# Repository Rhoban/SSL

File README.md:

# SSL - AI

## Development Guidelines

The code follows the guideline describe in ROS. [ROS_Guideline](http://wiki.ros.org/CppStyleGuide)

### Format

We using a .clang-format file. Caution ! Use the clang-format version 6.0, if your OS doesn't install it automatically then install clang-format-6.0 and rename the command to use the format script.

## Requirements

### System dependencies

You will need theses packets:

``` bash
sudo apt-get install -y g++ cmake libprotobuf-dev \
  protobuf-compiler php php-cli php-xml \
  libgtest-dev libwebsockets-dev gnuplot
```

To install the new viewer, we have conflits between the npm and the libwebsockets.
Go to here https://github.com/nodesource/distributions/blob/master/README.md and install npm.

### Catkin

Now install catkin:

``` bash
sudo apt-get install -y python-pip python-empy
# Eventually, if necessary, install python3-trollius
sudo apt-get install -y python3-trollius
sudo pip install -U catkin_tools
```

## Dependencies

After cloning this repository, run:

``` bash
./workspace setup
./workspace install
```

This will install all the dependencies.

See also clang-format above.

## Building

To build, run:

``` bash
./workspace build
```

Then, you can use the following debugging binaries:

* `./bin/vision`, to display informations from the vision (see `client/vision.cpp`)
* `./bin/referee`, to display informations from the referee (see `client/referee.cpp`)
* `./bin/sim`, to send commands to the simulator (see `client/sim.cpp`)

## Documentation

From workspace root:

``` bash
cd doc
mkdir build
cd build
cmake ..
make doc
```

Documentation is inside html directory.

## Testing

Tests can be built using the command: `./workspace tests`

To run the tests (once built), use the command: `./workspace test`

Access to the test message is controlled by adding the flag `--verbose`.

Example: Building and showing tests, but only for ssl_ai
`./workspace tests --verbose --no-deps ssl_ai`

## Packages

Here are the packages:

* `client`: the package to communicate with the SSL official software (vision, referee and simulator)
  * Note that this provides test binaries in `bin/` directory
* `viewer`: the viewer to interact with the strategies
* TODO!

## QtCreator

To use QtCreator, you have to add following line at the end of the file .workspace/SetupCommand.php:

below the line:

``` php
OS::run('catkin config --profile release -x _release --cmake-args -DCMAKE_BUILD_TYPE=Release -DCMAKE_CXX_FLAGS="-Wall -msse2"');
```

add the two lines:

``` php
OS::run('catkin config --profile qtcreator_debug -x _qtdebug --cmake-args -G"CodeBlocks - Unix Makefiles" -DCMAKE_BUILD_TYPE=Debug -DCMAKE_CXX_FLAGS="-Wall -msse2"');

OS::run('catkin config --profile qtcreator_release -x _qtrelease --cmake-args -G"CodeBlocks - Unix Makefiles" -DCMAKE_BUILD_TYPE=Release -DCMAKE_CXX_FLAGS="-Wall -msse2"');
```

This will create a debug and release profile with CodeBlocks support (needed by QtCreator).

Then:

``` bash
./workspace setup
./workspace build --profile=qtcreator_debug
./workspace build --profile=qtcreator_release
```

Now, you can load a CMakeLists.txt into QtCreator:

``` bash
qtcreator src/ai/CMakeLists.txt
```

In the configure project window, uncheck desktop and choose "import compil from..." and select `build_qtdebug/ssl_ai` then click on Import button. This will create a temporary imported kit with only one checked. You can add various setup (debug/release/...) by selecting the right building directory (i.e. build_qtrelease/ssl_ai).

Finally, click on "Configure Project" button.

If you want to reset your Qt configuration, just remove the file CMakeLists.txt.user. Also, please never add this file to the git repository.

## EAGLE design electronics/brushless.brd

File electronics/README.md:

# SSL Board

## XXX: To check!!!

- 5V tolerance for SPI
- 0-5V for maxon from 3.3??
  Add OD pullups?!
- Pull down on motors enable (or pull up?) to disable normally
- Maxon enable pin?

## Mechanics

Fixation holes are on a 126x82 rectangle, 3mm standoff

## Components

### MOS to kick

IRFPE30 (deprecated)
- http://fr.farnell.com/infineon/irfp4242pbf/transistor-mosfet-n-300v-to-247/dp/1298480

**OR** FDH44N50 (farnell 500V / 40A)
- http://fr.farnell.com/on-semiconductor-fairchild/fdh44n50/transistor-mosfet-n-to-247/dp/1095012

### NPN SOT-23 BC817 Transistors
- http://fr.farnell.com/nxp/bc817-215/transistor-npn-boitier-sot-23/dp/1081223

### TRACOPOWER TSR 1-2450 5V/1A Switching
- http://fr.farnell.com/tracopower/tsr-1-2450/convertisseur-dc-dc5v1asip/dp/1696320

### TRACOPOWER TSR 1-2433 3.3V/1A Switching

- http://fr.farnell.com/tracopower/tsr-1-2433/converter-dc-to-dc-3-3v-1a-sip/dp/1696319

### ~6.6mm pitch buzzer

- AliExpress ("passive buzzer") are typically 6.6mm pitch

### Infrared barrier (5mm LEDs/photodiode)

- Emit (100mA): http://fr.farnell.com/vishay/tsal6200/emetteur-ir-940nm-5mm-traversant/dp/3152856
- Receive: http://fr.farnell.com/osram/sfh213-fa/photodiode-ir-filtree/dp/1212763

### Quartz 40Mhz pour LS7366R-S

- http://fr.farnell.com/abracon/abl-40-000mhz-b2/crystal-40m-18pf-cl-hc49-4h/dp/1611785

### Multiplexers CD4051BM

- http://fr.farnell.com/texas-instruments/cd4051bm/circuit-logique-cmos-4000/dp/8388970

## Passives

- 0603 15pF capacitors
    - http://fr.farnell.com/multicomp/mcwr08x3300ftl/res-couche-epaisse-330r-1-0-125w/dp/2446955
- 0805 100 ohms resistor (stacked x3)
    -  http://fr.farnell.com/vishay/crcw080562r0fkea/res-couche-epaisse-62r-1-0-125w/dp/2138819
- 47uF decoupling capacitor
    - http://fr.farnell.com/panasonic-electronic-components/eee1ca470sp/condensateur-elec-alu-47uf-16v/dp/9696946

- 0805 1K resistor
- 0805 2K resistor
- 0805 3K resistor
- 0805 10K resistor

## Connectors

### 0.1" Header 2x8, right angle (communication modules)

- http://fr.farnell.com/samtec/ssw-104-02-g-d-ra/embase-2-54mm-coudee-double-8voies/dp/1668343

Or, for "on the table" version    

- http://fr.farnell.com/multicomp/2214s-08sg-85/fiche-femelle-ci-2-rangee-vert/dp/1593489

### 0.1" Header 1x8 + 0.1" Header 2x9 (maxon)

- http://fr.farnell.com/multicomp/2212s-08sg-85/fiche-femelle-ci-1-rangee-8voies/dp/1593463
- http://fr.farnell.com/samtec/bcs-109-l-d-te/femelle-2-54mm-vertical-18-voies/dp/2308429

### 0.1" Header 1x8 (IMU)

- http://fr.farnell.com/multicomp/2212s-08sg-85/fiche-femelle-ci-1-rangee-8voies/dp/1593463

### 0.1" Header 1x20 (Maple mini)

- http://fr.farnell.com/multicomp/2212s-20sg-85/fiche-femelle-ci-1-rangee-20voies/dp/1593469

### JST-XH 10 pins (2.54mm pitch)

- http://www.ebay.fr/itm/20-sets-JST-ZH-PH-XH-1-0-1-25MM-1-5-2-0-2-5-2p-6P-FemaleConnector-Plug-w-Wire/272410498870

### JST-ZH 2pin (1.5mm pitch)

- http://www.ebay.fr/itm/20-sets-JST-ZH-PH-XH-1-0-1-25MM-1-5-2-0-2-5-2p-6P-FemaleConnector-Plug-w-Wire/272410498870

### XT-60

- http://www.ebay.fr/itm/5-PAIRES-XT60-Connecteur-Prise-RC-Batterie-Accu-LiPO-Plug-3-5mm-Bullet-Connector/222301985053

## Sub-boards

- Maple mini
- GY-85
- Maxon 380200
- NRF24L01 modules
- Voltage booster (can be easily found with keywords "390V booster")

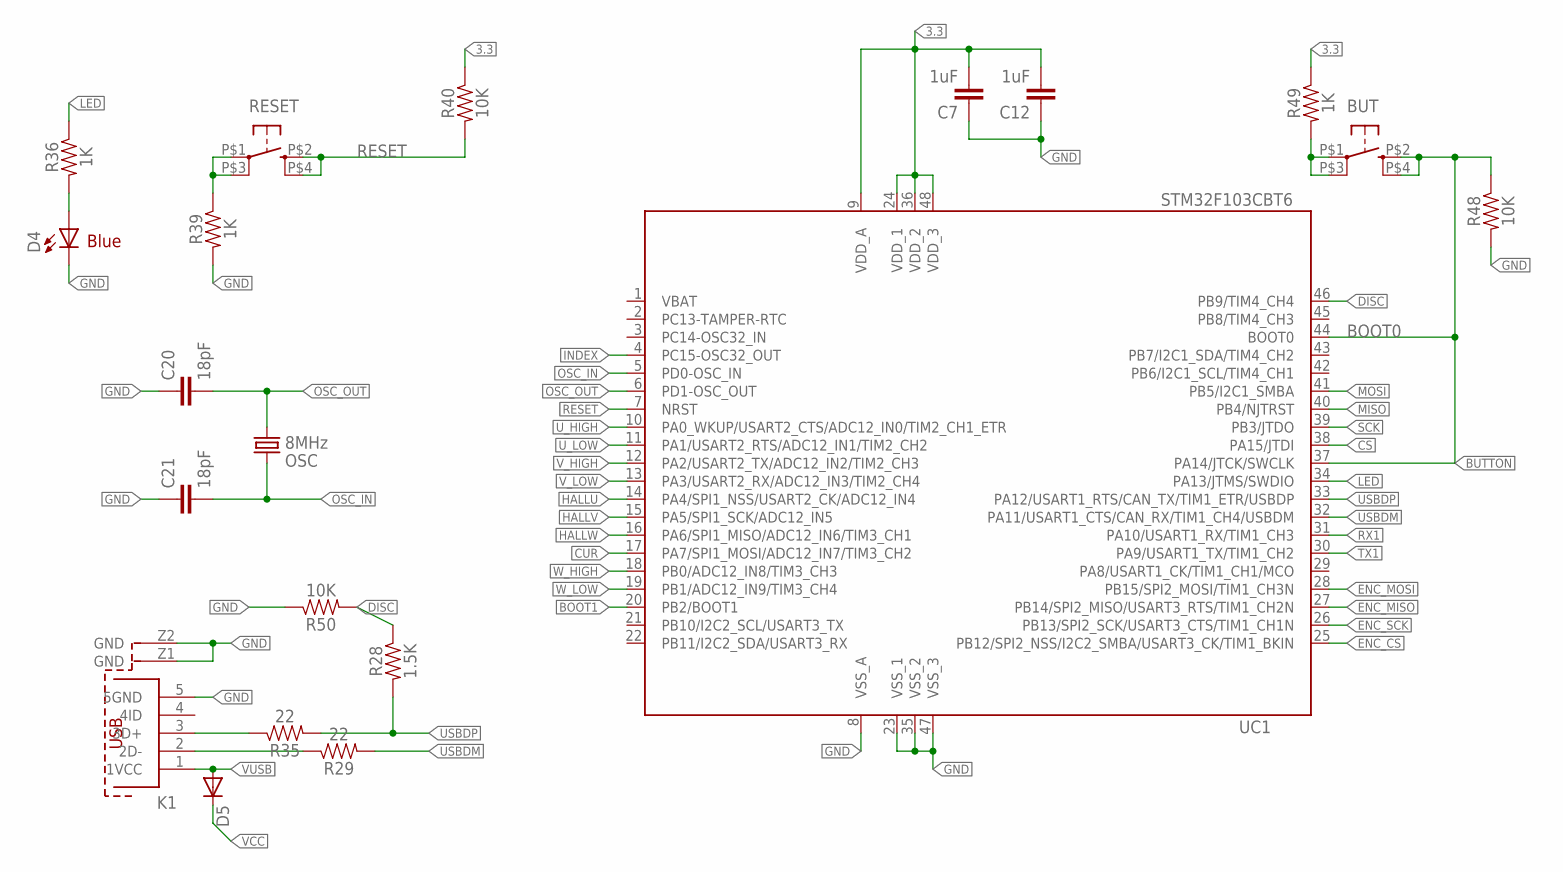
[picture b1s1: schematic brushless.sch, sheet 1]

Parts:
BUT: KMR211GLFS; PUSHBUTTON-KMR241GLFS; FARNELL 1437637
C7, C12: 1uF; 0805@1; FARNELL 2496946
C20, C21: 18pF; 0805@1; FARNELL 1414620
D4: Blue; LED-1206; FARNELL 1581233
D5: DIODESOD; SOD-323; FARNELL 8737843RL
K1: 614105150721; FARNELL 2470830
OSC: 8MHz; CRYSTAL-SMD-5X3; FARNELL 2467818
R28: 1.5K; 0805; FARNELL 2446909
R29, R35: 22; 0805; FARNELL 2446926
R36, R39, R49: 1K; 0805; FARNELL 2446904
R40, R48, R50: 10K; 0805; FARNELL 2447553
RESET: KMR211GLFS; PUSHBUTTON-KMR241GLFS; FARNELL 1437637
UC1: STM32F103CBT6; LQFP48; FARNELL 1606327

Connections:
3.3: C7.2, C12.2, R40.1, R49.1, UC1.9 (VDD_A), UC1.24 (VDD_1), UC1.36 (VDD_2), UC1.48 (VDD_3); also elsewhere on the board
BOOT1: UC1.20 (PB2/BOOT1)
BUTTON: BUT.P$2 (2), BUT.P$4 (4), R48.1, UC1.37 (PA14/JTCK/SWCLK), UC1.44 (BOOT0)
CS: UC1.38 (PA15/JTDI); also elsewhere on the board
CUR: UC1.17 (PA7/SPI1_MOSI/ADC12_IN7/TIM3_CH2); also elsewhere on the board
DISC: R28.1, R50.2, UC1.46 (PB9/TIM4_CH4)
ENC_CS: UC1.25 (PB12/SPI2_NSS/I2C2_SMBA/USART3_CK/TIM1_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); also elsewhere on the board
ENC_MISO: UC1.27 (PB14/SPI2_MISO/USART3_RTS/TIM1_CH2N); also elsewhere on the board
ENC_MOSI: UC1.28 (PB15/SPI2_MOSI/TIM1_CH3N); also elsewhere on the board
ENC_SCK: UC1.26 (PB13/SPI2_SCK/USART3_CTS/TIM1_CH1N); also elsewhere on the board
GND: C7.1, C12.1, C20.1, C21.1, D4.C, K1.5 (5GND), K1.Z1 (GND), K1.Z2 (GND), R39.2, R48.2, R50.1, UC1.8 (VSS_A), UC1.23 (VSS_1), UC1.35 (VSS_2), UC1.47 (VSS_3); also elsewhere on the board
HALLU: UC1.14 (PA4/SPI1_NSS/USART2_CK/ADC12_IN4); also elsewhere on the board
HALLV: UC1.15 (PA5/SPI1_SCK/ADC12_IN5); also elsewhere on the board
HALLW: UC1.16 (PA6/SPI1_MISO/ADC12_IN6/TIM3_CH1); also elsewhere on the board
INDEX: UC1.4 (PC15-OSC32_OUT); also elsewhere on the board
LED: R36.1, UC1.34 (PA13/JTMS/SWDIO)
MISO: UC1.40 (PB4/NJTRST); also elsewhere on the board
MOSI: UC1.41 (PB5/I2C1_SMBA); also elsewhere on the board
unnamed: R39.1, RESET.P$1 (1), RESET.P$3 (3)
unnamed: BUT.P$1 (1), BUT.P$3 (3), R49.2
unnamed: D4.A, R36.2
unnamed: K1.2 (2D-), R29.1
unnamed: K1.3 (3D+), R35.1
OSC_IN: C21.2, OSC.3 (2), UC1.5 (PD0-OSC_IN)
OSC_OUT: C20.2, OSC.1, UC1.6 (PD1-OSC_OUT)
RESET: R40.2, RESET.P$2 (2), RESET.P$4 (4), UC1.7 (NRST)
RX1: UC1.31 (PA10/USART1_RX/TIM1_CH3)
SCK: UC1.39 (PB3/JTDO); also elsewhere on the board
TX1: UC1.30 (PA9/USART1_TX/TIM1_CH2)
USBDM: R29.2, UC1.32 (PA11/USART1_CTS/CAN_RX/TIM1_CH4/USBDM)
USBDP: R28.2, R35.2, UC1.33 (PA12/USART1_RTS/CAN_TX/TIM1_ETR/USBDP)
U_HIGH: UC1.10 (PA0_WKUP/USART2_CTS/ADC12_IN0/TIM2_CH1_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); also elsewhere on the board
U_LOW: UC1.11 (PA1/USART2_RTS/ADC12_IN1/TIM2_CH2); also elsewhere on the board
VBAT: UC1.1 (VBAT)
VCC: D5.1 (C); also elsewhere on the board
VUSB: D5.2 (A), K1.1 (1VCC)
V_HIGH: UC1.12 (PA2/USART2_TX/ADC12_IN2/TIM2_CH3); also elsewhere on the board
V_LOW: UC1.13 (PA3/USART2_RX/ADC12_IN3/TIM2_CH4); also elsewhere on the board
W_HIGH: UC1.18 (PB0/ADC12_IN8/TIM3_CH3); also elsewhere on the board
W_LOW: UC1.19 (PB1/ADC12_IN9/TIM3_CH4); also elsewhere on the board

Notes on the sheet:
BOOT0
Blue

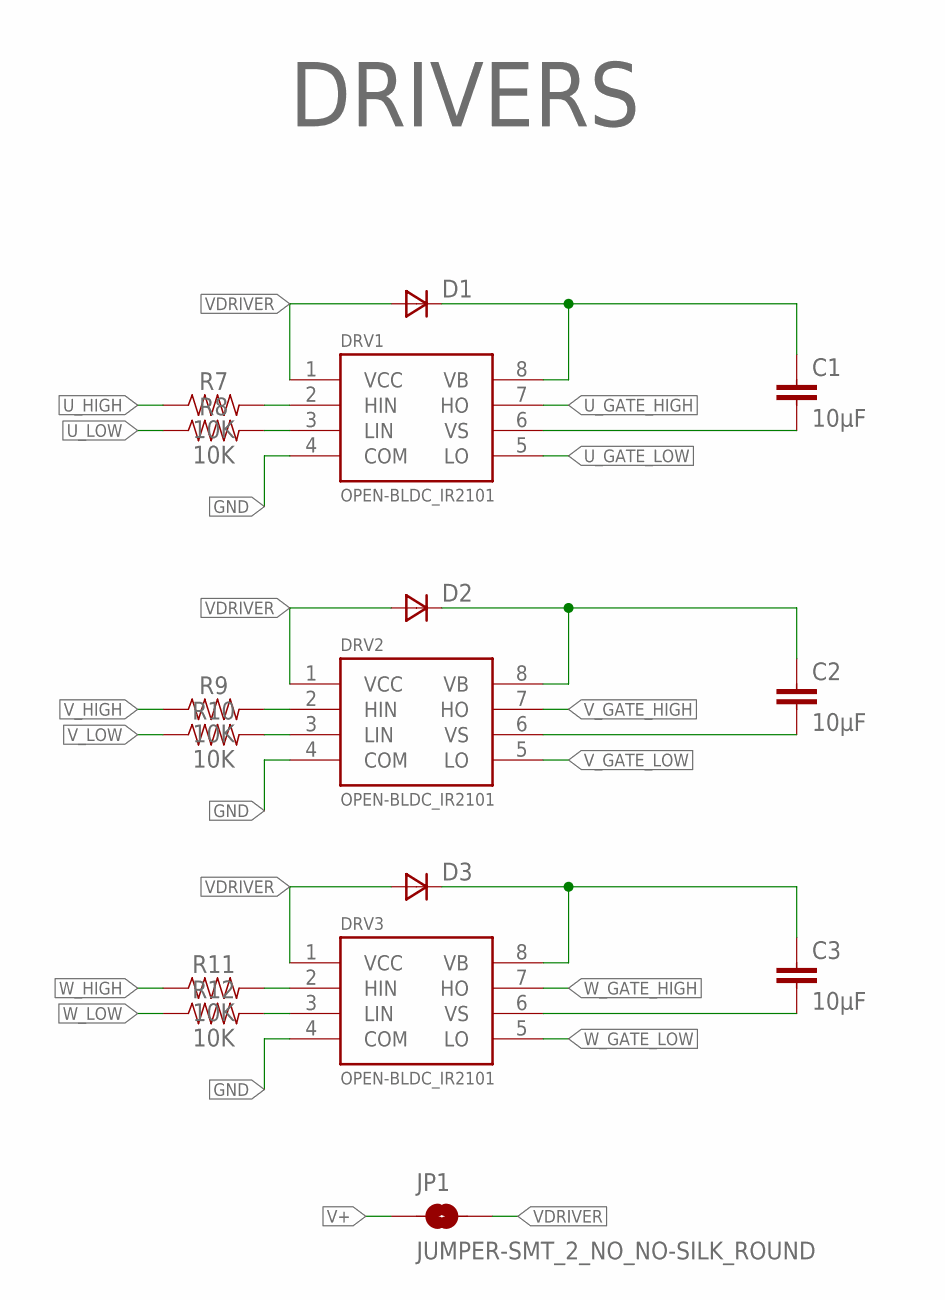
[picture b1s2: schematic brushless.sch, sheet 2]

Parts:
C1, C2, C3: 10µF; 0805; FARNELL 2528772
D1, D2, D3: ZETEX_VAR2SOT23; ZETEX_SOT-23; FARNELL 2317446
DRV1, DRV2, DRV3: OPEN-BLDC_IR2101; OPEN-BLDC_SO-8; FARNELL 2296000
JP1: JUMPER-SMT_2_NO_NO-SILK_ROUND; SMT-JUMPER_2_NO_NO-SILK_ROUND
R7, R8, R9, R10, R11, R12: 10K; 0805; FARNELL 2447553

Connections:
GND: DRV1.4 (COM), DRV2.4 (COM), DRV3.4 (COM); also elsewhere on the board
unnamed: DRV1.2 (HIN), R7.2
unnamed: C1.1, D1.1 (C), DRV1.8 (VB)
unnamed: DRV1.3 (LIN), R8.2
unnamed: C2.1, D2.1 (C), DRV2.8 (VB)
unnamed: C1.2, DRV1.6 (VS)
unnamed: DRV2.2 (HIN), R9.2
unnamed: DRV2.3 (LIN), R10.2
unnamed: C2.2, DRV2.6 (VS)
unnamed: C3.1, D3.1 (C), DRV3.8 (VB)
unnamed: DRV3.2 (HIN), R11.2
unnamed: DRV3.3 (LIN), R12.2
unnamed: C3.2, DRV3.6 (VS)
U_GATE_HIGH: DRV1.7 (HO); also elsewhere on the board
U_GATE_LOW: DRV1.5 (LO); also elsewhere on the board
U_HIGH: R7.1; also elsewhere on the board
U_LOW: R8.1; also elsewhere on the board
V+: JP1.1; also elsewhere on the board
VDRIVER: D1.3 (A), D2.3 (A), D3.3 (A), DRV1.1 (VCC), DRV2.1 (VCC), DRV3.1 (VCC), JP1.2; also elsewhere on the board
V_GATE_HIGH: DRV2.7 (HO); also elsewhere on the board
V_GATE_LOW: DRV2.5 (LO); also elsewhere on the board
V_HIGH: R9.1; also elsewhere on the board
V_LOW: R10.1; also elsewhere on the board
W_GATE_HIGH: DRV3.7 (HO); also elsewhere on the board
W_GATE_LOW: DRV3.5 (LO); also elsewhere on the board
W_HIGH: R11.1; also elsewhere on the board
W_LOW: R12.1; also elsewhere on the board

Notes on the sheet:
DRIVERS

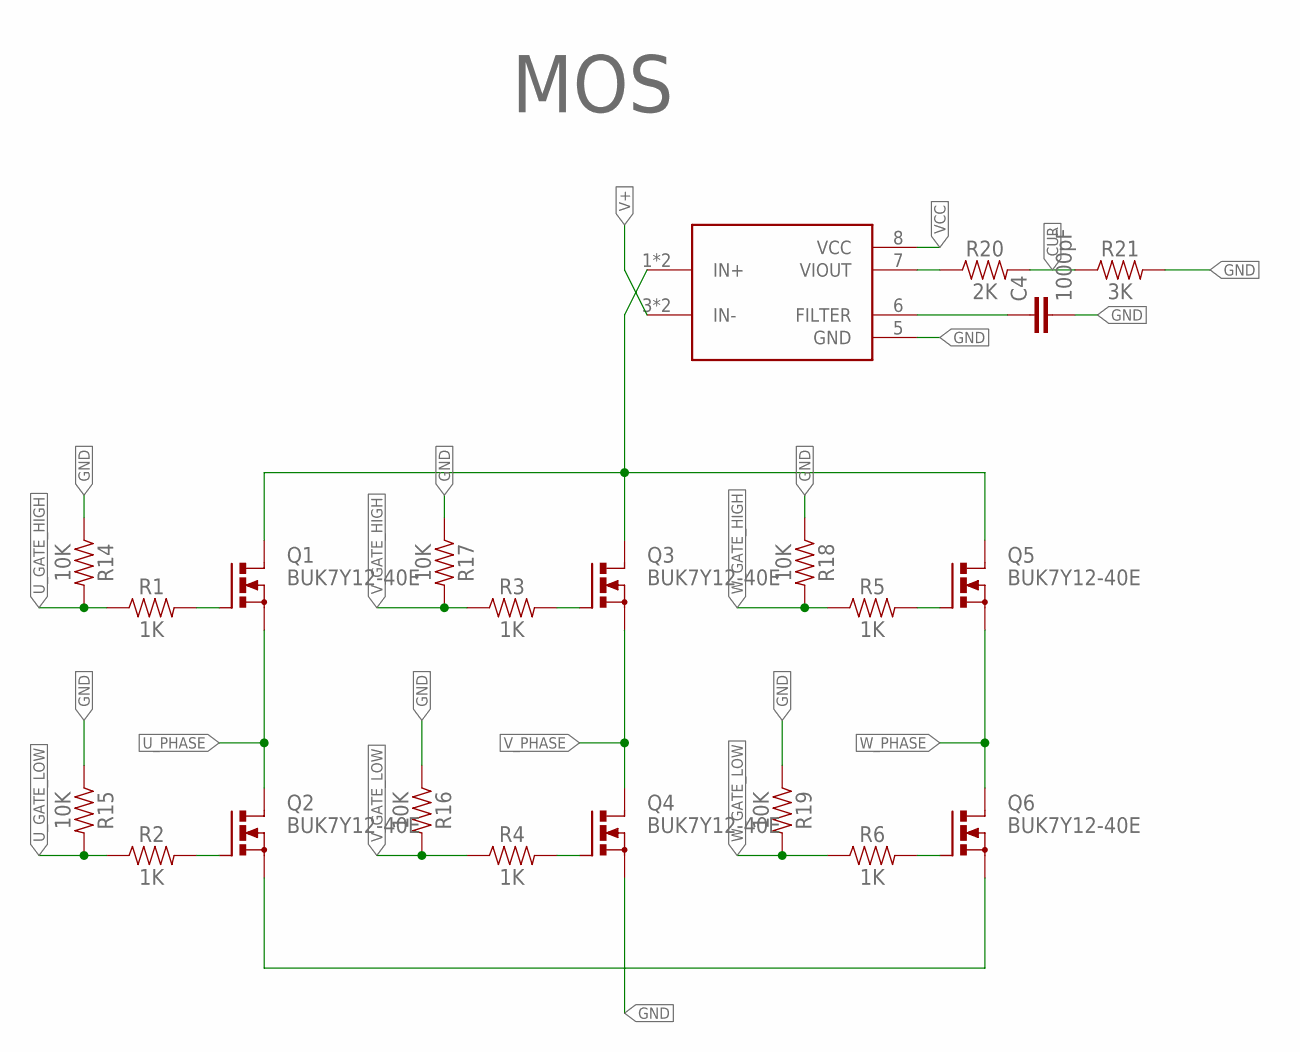
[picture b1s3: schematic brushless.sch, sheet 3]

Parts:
C4: 1000pF; 0805@1; FARNELL 2496935
Q1, Q2, Q3, Q4, Q5, Q6: BUK7Y12-40E; SOT669; FARNELL 2319916
R1, R2, R3, R4, R5, R6: 1K; 0805; FARNELL 2446904
R14, R15, R16, R17, R18, R19: 10K; 0805; FARNELL 2447553
R20: 2K; 0805; FARNELL 2446939
R21: 3K; 0805; FARNELL 2446965
SENSE: ACS712; SO8; FARNELL 1329624

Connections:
CUR: R20.2, R21.1; also elsewhere on the board
GND: C4.2, Q2.1 (S), Q2.2 (S), Q2.3 (S), Q4.1 (S), Q4.2 (S), Q4.3 (S), Q6.1 (S), Q6.2 (S), Q6.3 (S), R14.1, R15.1, R16.1, R17.1, R18.1, R19.1, R21.2, SENSE.5 (GND); also elsewhere on the board
unnamed: Q1.4 (G), R1.2
unnamed: Q3.4 (G), R3.2
unnamed: Q2.4 (G), R2.2
unnamed: Q4.4 (G), R4.2
unnamed: Q5.4 (G), R5.2
unnamed: Q6.4 (G), R6.2
unnamed: R20.1, SENSE.7 (VIOUT)
unnamed: C4.1, SENSE.6 (FILTER)
U_GATE_HIGH: R1.1, R14.2; also elsewhere on the board
U_GATE_LOW: R2.1, R15.2; also elsewhere on the board
U_PHASE: Q1.1 (S), Q1.2 (S), Q1.3 (S), Q2.MB (D); also elsewhere on the board
V+: SENSE.3 (IN-), SENSE.4 (IN-); also elsewhere on the board
V+_MOS: Q1.MB (D), Q3.MB (D), Q5.MB (D), SENSE.1 (IN+), SENSE.2 (IN+)
VCC: SENSE.8 (VCC); also elsewhere on the board
V_GATE_HIGH: R3.1, R17.2; also elsewhere on the board
V_GATE_LOW: R4.1, R16.2; also elsewhere on the board
V_PHASE: Q3.1 (S), Q3.2 (S), Q3.3 (S), Q4.MB (D); also elsewhere on the board
W_GATE_HIGH: R5.1, R18.2; also elsewhere on the board
W_GATE_LOW: R6.1, R19.2; also elsewhere on the board
W_PHASE: Q5.1 (S), Q5.2 (S), Q5.3 (S), Q6.MB (D); also elsewhere on the board

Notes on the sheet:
MOS

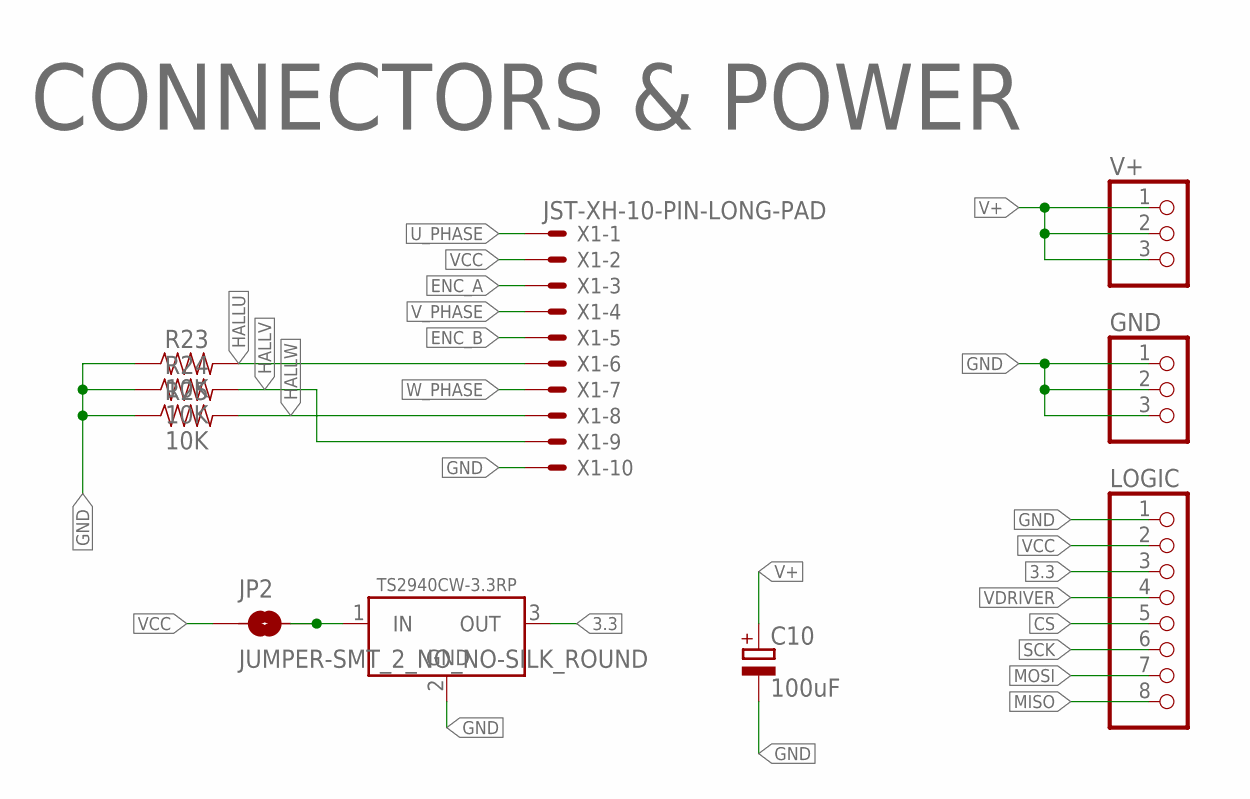
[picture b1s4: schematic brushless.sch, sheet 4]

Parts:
C10: 100uF; E3,5-8; FARNELL 1144713
GND: CONNEC_1X03; FARNELL 1022248
JP2: JUMPER-SMT_2_NO_NO-SILK_ROUND; SMT-JUMPER_2_NO_NO-SILK_ROUND
LOGIC: CONNEC_1X08; FARNELL 1022256
R23, R24, R25: 10K; 0805; FARNELL 2447553
REG1: TS2940CW-3.3RP; SOT223; FARNELL 7261403
V+: CONNEC_1X03; FARNELL 1022248
X1: JST-XH-10-PIN-LONG-PAD; JST-XH-10-PACKAGE-LONG-PAD

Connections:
3.3: LOGIC.3, REG1.3 (OUT); also elsewhere on the board
CS: LOGIC.5; also elsewhere on the board
ENC_A: X1.3; also elsewhere on the board
ENC_B: X1.5; also elsewhere on the board
GND: C10.-, GND.1, GND.2, GND.3, LOGIC.1, R23.1, R24.1, R25.1, REG1.2 (GND), X1.10; also elsewhere on the board
HALLU: R23.2, X1.6; also elsewhere on the board
HALLV: R24.2, X1.9; also elsewhere on the board
HALLW: R25.2, X1.8; also elsewhere on the board
MISO: LOGIC.8; also elsewhere on the board
MOSI: LOGIC.7; also elsewhere on the board
unnamed: JP2.2, REG1.1 (IN)
SCK: LOGIC.6; also elsewhere on the board
U_PHASE: X1.1; also elsewhere on the board
V+: C10.+, V+.1, V+.2, V+.3; also elsewhere on the board
VCC: JP2.1, LOGIC.2, X1.2; also elsewhere on the board
VDRIVER: LOGIC.4; also elsewhere on the board
V_PHASE: X1.4; also elsewhere on the board
W_PHASE: X1.7; also elsewhere on the board

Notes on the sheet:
CONNECTORS & POWER

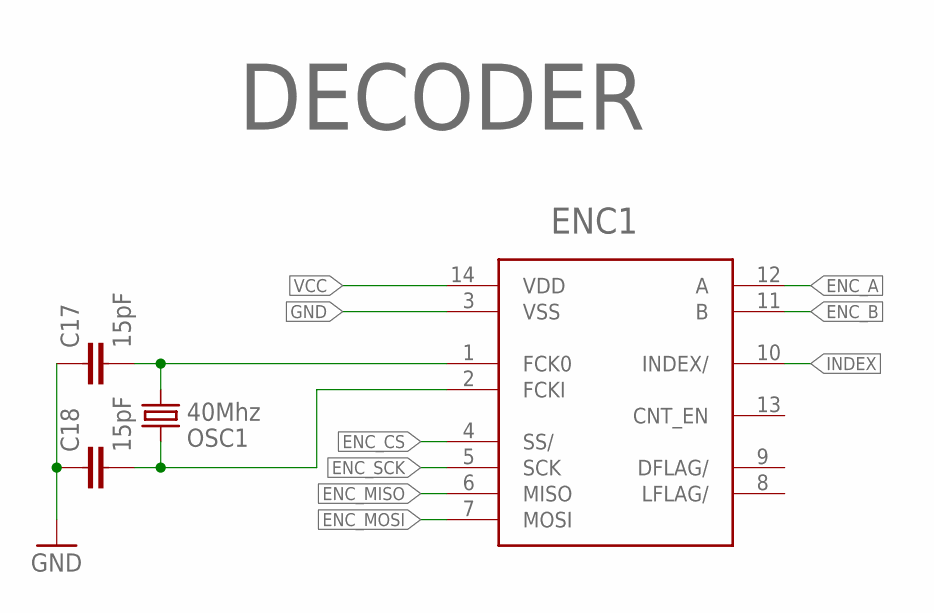
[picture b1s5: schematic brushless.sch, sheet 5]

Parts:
C17, C18: 15pF; C0603; FARNELL 721980
ENC1: LS7366RSO14; SO14
OSC1: 40Mhz; CRYSTAL-SMD-5X3; FARNELL 1842013

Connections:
ENC_A: ENC1.12 (A); also elsewhere on the board
ENC_B: ENC1.11 (B); also elsewhere on the board
ENC_CS: ENC1.4 (SS/); also elsewhere on the board
ENC_MISO: ENC1.6 (MISO); also elsewhere on the board
ENC_MOSI: ENC1.7 (MOSI); also elsewhere on the board
ENC_SCK: ENC1.5 (SCK); also elsewhere on the board
GND: C17.1, C18.1, ENC1.3 (VSS); also elsewhere on the board
INDEX: ENC1.10 (INDEX/); also elsewhere on the board
unnamed: C17.2, ENC1.1 (FCK0), OSC1.1
unnamed: C18.2, ENC1.2 (FCKI), OSC1.3 (2)
VCC: ENC1.14 (VDD); also elsewhere on the board

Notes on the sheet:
DECODER

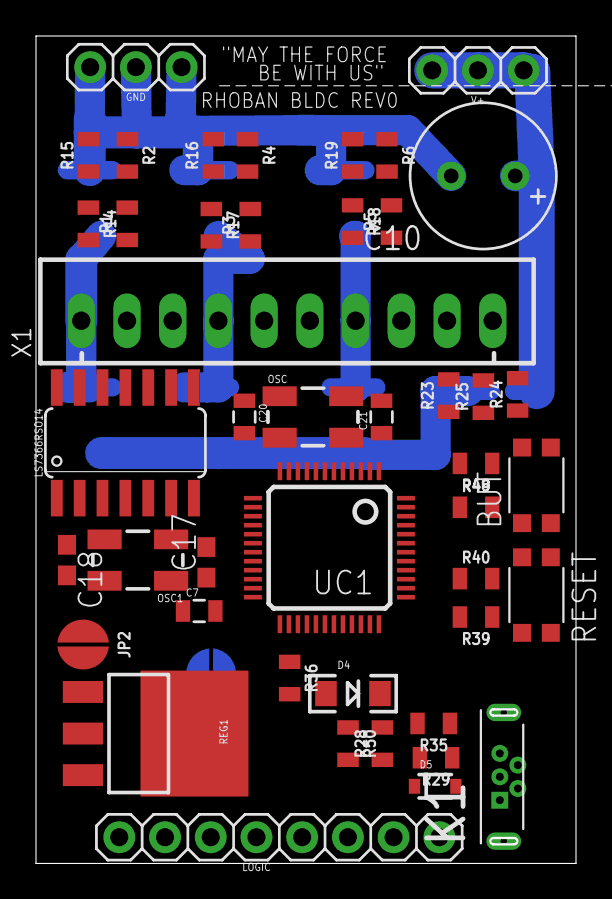
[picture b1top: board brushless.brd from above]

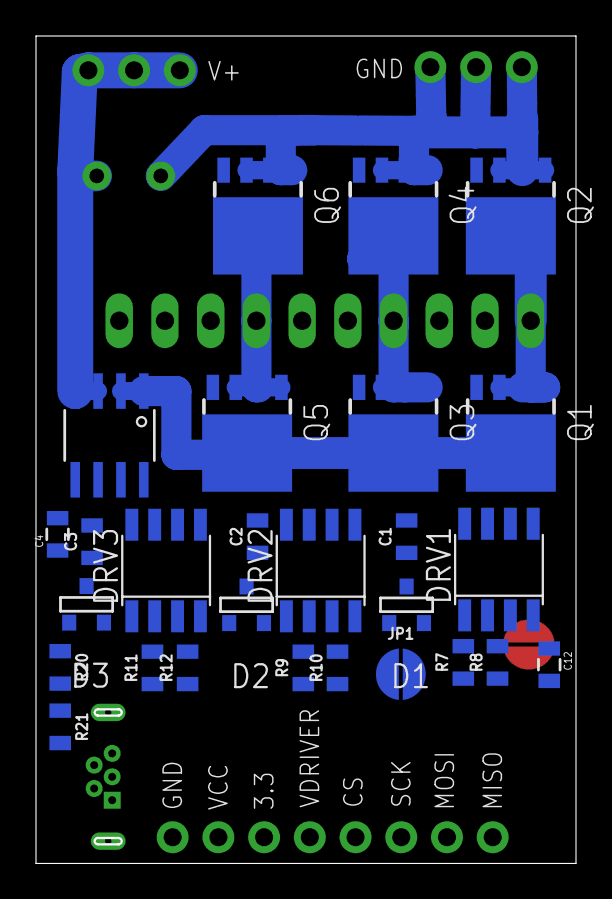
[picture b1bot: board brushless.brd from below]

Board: 4 copper layers, 30.0 x 46.0 mm, 72 parts (27 on the bottom side), 73 nets.

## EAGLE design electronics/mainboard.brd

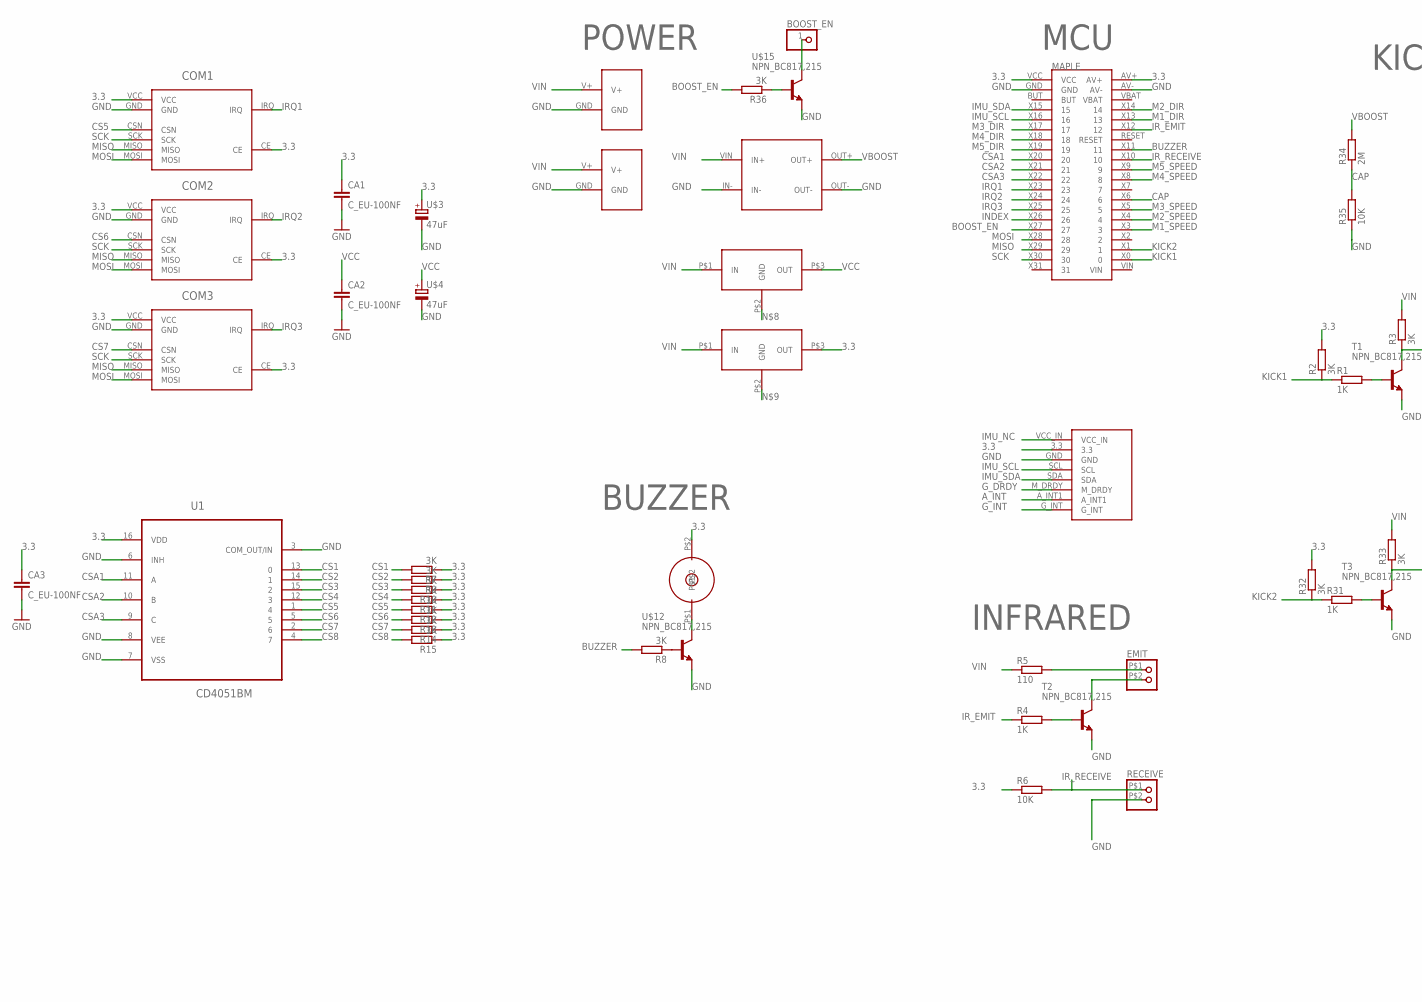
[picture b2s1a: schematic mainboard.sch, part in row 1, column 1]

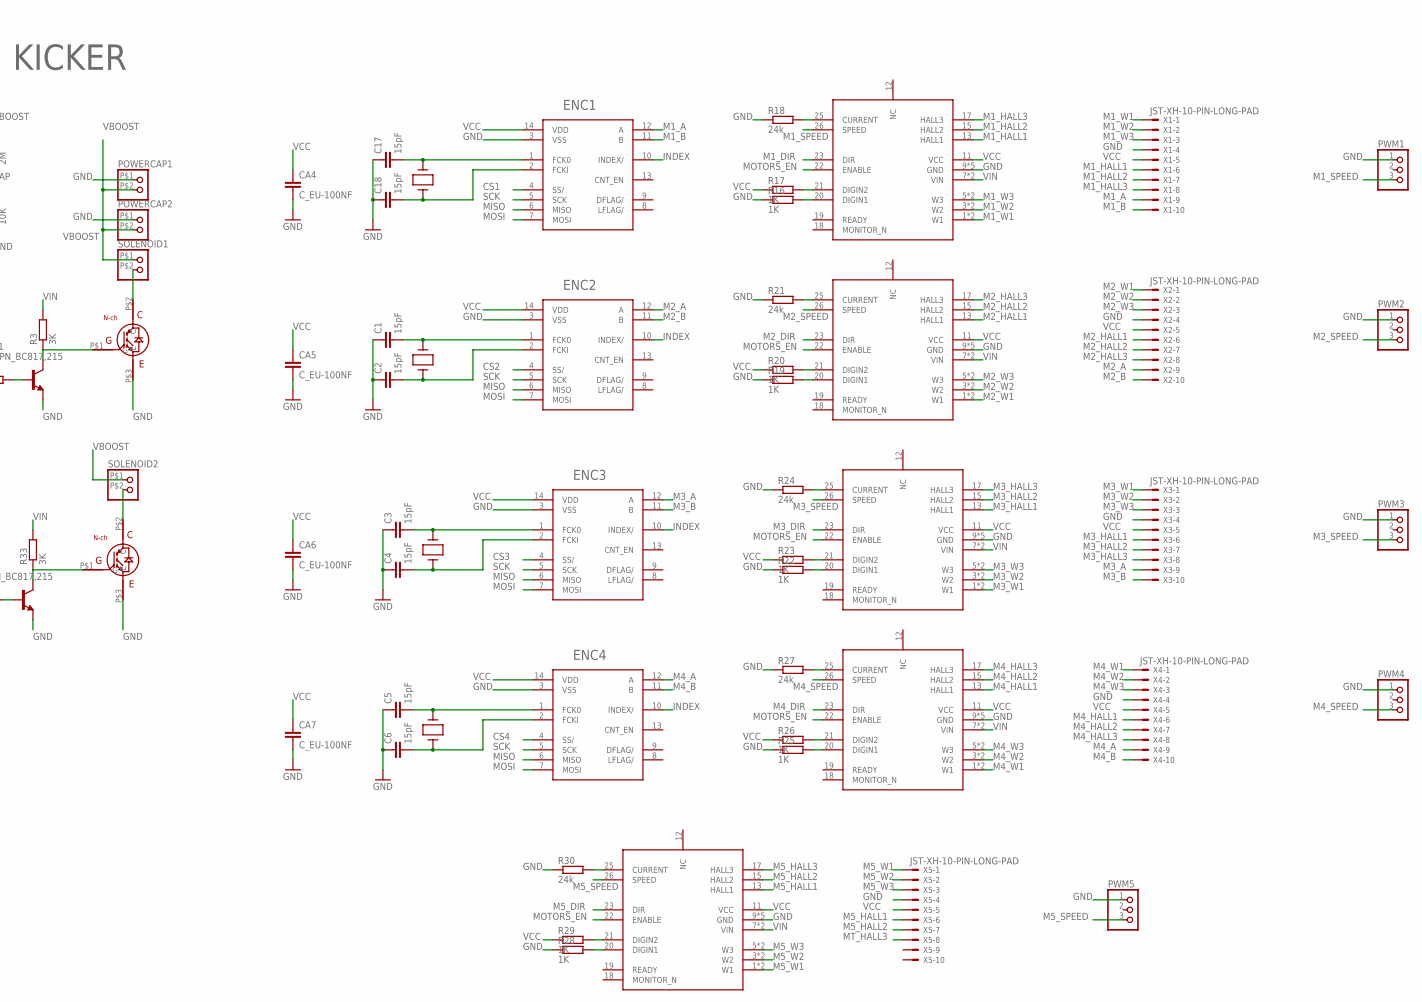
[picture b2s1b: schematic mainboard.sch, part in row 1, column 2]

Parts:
BOOST_EN: CONNEC_1X01
C1, C2, C3, C4, C5, C6, C17, C18: 15pF; C0603
CA1, CA2, CA3, CA4, CA5, CA6, CA7: C_EU-100NF; C0805
COM1, COM2, COM3: NRF24L01
EMIT: CONNEC_1X02JST-ZH; JST_ZH_2P
ENC1, ENC2, ENC3, ENC4: LS7366RSO14; SO14
MAPLE: MAPLE_MINI; CONNEC_2X20
POWERCAP1, POWERCAP2: CONNEC_1X02BIG; CONNEC_1X02_BIG
PWM1, PWM2, PWM3, PWM4, PWM5: CONNEC_1X03
R1, R4, R16, R17, R19, R20, R22, R23, R25, R26, R28, R29, R31: 1K; R0805
R2, R3, R7, R8, R9, R10, R11, R12, R13, R14, R15, R32, R33, R36: 3K; R0805
R5: 110; R0805
R6, R35: 10K; R0805
R18, R21, R24, R27, R30: 24k; R0805
R34: 2M; R0805
RECEIVE: CONNEC_1X02JST-ZH; JST_ZH_2P
REG3.3V, REG5V: REG_5V; TRACOPOWER
SOLENOID1, SOLENOID2: CONNEC_1X02BIG; CONNEC_1X02_BIG
T1, T2, T3: NPN_BC817,215; SOT-23
U1: CD4051BM; SOIC127P600X175-16N
U$1, U$11: TO-247A; TO-247
U$2: GY-85
U$3, U$4: 47uF; PANASONIC_D
U$5: BOOSTER; BOOSTER_390V
U$6, U$7, U$8, U$9, U$10: MAXON380200
U$12, U$15: NPN_BC817,215; SOT-23
U$13: BUZZER66
X1, X2, X3, X4, X5: JST-XH-10-PIN-LONG-PAD; JST-XH-10-PACKAGE-LONG-PAD
XT1, XT60: CONNEC_ALIM; XT60
XTAL1, XTAL2, XTAL3, XTAL4: 40Mhz; HC49US

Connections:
3.3: CA1.1, CA3.1, COM1.CE, COM1.VCC, COM2.CE, COM2.VCC, COM3.CE, COM3.VCC, MAPLE.AV+, MAPLE.VCC, R2.2, R6.1, R7.1, R9.1, R10.1, R11.1, R12.1, R13.1, R14.1, R15.1, R32.2, REG3.3V.P$3 (OUT), U1.16 (VDD), U$2.3.3, U$3.+, U$13.P$2
A_INT: U$2.A_INT1
BOOST_EN: MAPLE.X27 (27), R36.2
BUZZER: MAPLE.X11 (11), R8.2
CAP: MAPLE.X6 (6), R34.1, R35.2
CS1: ENC1.4 (SS/), R7.2, U1.13 (0)
CS2: ENC2.4 (SS/), R9.2, U1.14 (1)
CS3: ENC3.4 (SS/), R10.2, U1.15 (2)
CS4: ENC4.4 (SS/), R11.2, U1.12 (3)
CS5: COM1.CSN, R12.2, U1.1 (4)
CS6: COM2.CSN, R13.2, U1.5
CS7: COM3.CSN, R14.2, U1.2 (6)
CS8: R15.2, U1.4 (7)
CSA1: MAPLE.X20 (20), U1.11 (A)
CSA2: MAPLE.X21 (21), U1.10 (B)
CSA3: MAPLE.X22 (22), U1.9 (C)
GND: C1.1, C2.1, C3.1, C4.1, C5.1, C6.1, C17.1, C18.1, CA1.2, CA2.2, CA3.2, CA4.2, CA5.2, CA6.2, CA7.2, COM1.GND, COM2.GND, COM3.GND, ENC1.3 (VSS), ENC2.3 (VSS), ENC3.3 (VSS), ENC4.3 (VSS), MAPLE.AV-, MAPLE.GND, POWERCAP1.P$1 (1), POWERCAP2.P$1 (1), PWM1.1, PWM2.1, PWM3.1, PWM4.1, PWM5.1, R16.1, R18.1, R19.1, R21.1, R22.1, R24.1, R25.1, R27.1, R28.1, R30.1, R35.1, RECEIVE.P$2 (2), T1.2 (E), T2.2 (E), T3.2 (E), U1.3 (COM_OUT/IN), U1.6 (INH), U1.7 (VSS), U1.8 (VEE), U$1.P$3 (E), U$2.GND, U$3.-, U$4.-, U$5.IN-, U$5.OUT-, U$6.9 (GND), U$6.10 (GND), U$6.14 (GND), U$6.16 (GND), U$6.24 (GND), U$7.9 (GND), U$7.10 (GND), U$7.14 (GND), U$7.16 (GND), U$7.24 (GND), U$8.9 (GND), U$8.10 (GND), U$8.14 (GND), U$8.16 (GND), U$8.24 (GND), U$9.9 (GND), U$9.10 (GND), U$9.14 (GND), U$9.16 (GND), U$9.24 (GND), U$10.9 (GND), U$10.10 (GND), U$10.14 (GND), U$10.16 (GND), U$10.24 (GND), U$11.P$3 (E), U$12.2 (E), U$15.2 (E), X1.4, X2.4, X3.4, X4.4, X5.4, XT1.GND, XT60.GND
G_DRDY: U$2.M_DRDY
G_INT: U$2.G_INT
IMU_NC: U$2.VCC_IN
IMU_SCL: MAPLE.X16 (16), U$2.SCL
IMU_SDA: MAPLE.X15 (15), U$2.SDA
INDEX: ENC1.10 (INDEX/), ENC2.10 (INDEX/), ENC3.10 (INDEX/), ENC4.10 (INDEX/), MAPLE.X26 (26)
IRQ1: COM1.IRQ, MAPLE.X23 (23)
IRQ2: COM2.IRQ, MAPLE.X24 (24)
IRQ3: COM3.IRQ, MAPLE.X25 (25)
IR_EMIT: MAPLE.X12 (12), R4.1
IR_RECEIVE: MAPLE.X10 (10), R6.2, RECEIVE.P$1 (1)
KICK1: MAPLE.X0 (0), R1.1, R2.1
KICK2: MAPLE.X1 (1), R31.1, R32.1
M1_A: ENC1.12 (A), X1.9
M1_B: ENC1.11 (B), X1.10
M1_DIR: MAPLE.X13 (13), U$6.23 (DIR)
M1_HALL1: U$6.13 (HALL1), X1.6
M1_HALL2: U$6.15 (HALL2), X1.7
M1_HALL3: U$6.17 (HALL3), X1.8
M1_SPEED: MAPLE.X3 (3), PWM1.3, U$6.26 (SPEED)
M1_W1: U$6.1 (W1), U$6.2 (W1), X1.1
M1_W2: U$6.3 (W2), U$6.4 (W2), X1.2
M1_W3: U$6.5 (W3), U$6.6 (W3), X1.3
M2_A: ENC2.12 (A), X2.9
M2_B: ENC2.11 (B), X2.10
M2_DIR: MAPLE.X14 (14), U$7.23 (DIR)
M2_HALL1: U$7.13 (HALL1), X2.6
M2_HALL2: U$7.15 (HALL2), X2.7
M2_HALL3: U$7.17 (HALL3), X2.8
M2_SPEED: MAPLE.X4 (4), PWM2.3, U$7.26 (SPEED)
M2_W1: U$7.1 (W1), U$7.2 (W1), X2.1
M2_W2: U$7.3 (W2), U$7.4 (W2), X2.2
M2_W3: U$7.5 (W3), U$7.6 (W3), X2.3
M3_A: ENC3.12 (A), X3.9
M3_B: ENC3.11 (B), X3.10
M3_DIR: MAPLE.X17 (17), U$8.23 (DIR)
M3_HALL1: U$8.13 (HALL1), X3.6
M3_HALL2: U$8.15 (HALL2), X3.7
M3_HALL3: U$8.17 (HALL3), X3.8
M3_SPEED: MAPLE.X5 (5), PWM3.3, U$8.26 (SPEED)
M3_W1: U$8.1 (W1), U$8.2 (W1), X3.1
M3_W2: U$8.3 (W2), U$8.4 (W2), X3.2
M3_W3: U$8.5 (W3), U$8.6 (W3), X3.3
M4_A: ENC4.12 (A), X4.9
M4_B: ENC4.11 (B), X4.10
M4_DIR: MAPLE.X18 (18), U$9.23 (DIR)
M4_HALL1: U$9.13 (HALL1), X4.6
M4_HALL2: U$9.15 (HALL2), X4.7
M4_HALL3: U$9.17 (HALL3), X4.8
M4_SPEED: MAPLE.X8 (8), PWM4.3, U$9.26 (SPEED)
M4_W1: U$9.1 (W1), U$9.2 (W1), X4.1
M4_W2: U$9.3 (W2), U$9.4 (W2), X4.2
M4_W3: U$9.5 (W3), U$9.6 (W3), X4.3
M5_DIR: MAPLE.X19 (19), U$10.23 (DIR)
M5_HALL1: U$10.13 (HALL1), X5.6
M5_HALL2: U$10.15 (HALL2), X5.7
M5_HALL3: U$10.17 (HALL3)
M5_SPEED: MAPLE.X9 (9), PWM5.3, U$10.26 (SPEED)
M5_W1: U$10.1 (W1), U$10.2 (W1), X5.1
M5_W2: U$10.3 (W2), U$10.4 (W2), X5.2
M5_W3: U$10.5 (W3), U$10.6 (W3), X5.3
MISO: COM1.MISO, COM2.MISO, COM3.MISO, ENC1.6 (MISO), ENC2.6 (MISO), ENC3.6 (MISO), ENC4.6 (MISO), MAPLE.X29 (29)
MOSI: COM1.MOSI, COM2.MOSI, COM3.MOSI, ENC1.7 (MOSI), ENC2.7 (MOSI), ENC3.7 (MOSI), ENC4.7 (MOSI), MAPLE.X28 (28)
MOTORS_EN: U$6.22 (ENABLE), U$7.22 (ENABLE), U$8.22 (ENABLE), U$9.22 (ENABLE), U$10.22 (ENABLE)
MT_HALL3: X5.8
unnamed: R1.2, T1.1 (B)
unnamed: SOLENOID1.P$2 (2), U$1.P$2 (C)
unnamed: R8.1, U$12.1 (B)
unnamed: R3.1, T1.3 (C), U$1.P$1 (G)
unnamed: U$12.3 (C), U$13.P$1
unnamed: EMIT.P$1 (1), R5.2
unnamed: EMIT.P$2 (2), T2.3 (C)
unnamed: R16.2, U$6.20 (DIGIN1)
unnamed: R4.2, T2.1 (B)
unnamed: R17.2, U$6.21 (DIGIN2)
unnamed: C1.2, ENC2.1 (FCK0), XTAL2.2
unnamed: C2.2, ENC2.2 (FCKI), XTAL2.1
unnamed: R19.2, U$7.20 (DIGIN1)
unnamed: R18.2, U$6.25 (CURRENT)
unnamed: R31.2, T3.1 (B)
unnamed: R20.2, U$7.21 (DIGIN2)
unnamed: C17.2, ENC1.1 (FCK0), XTAL1.2
unnamed: C18.2, ENC1.2 (FCKI), XTAL1.1
unnamed: R21.2, U$7.25 (CURRENT)
unnamed: C3.2, ENC3.1 (FCK0), XTAL3.2
unnamed: C4.2, ENC3.2 (FCKI), XTAL3.1
unnamed: R22.2, U$8.20 (DIGIN1)
unnamed: R23.2, U$8.21 (DIGIN2)
unnamed: R24.2, U$8.25 (CURRENT)
unnamed: C5.2, ENC4.1 (FCK0), XTAL4.2
unnamed: C6.2, ENC4.2 (FCKI), XTAL4.1
unnamed: R25.2, U$9.20 (DIGIN1)
unnamed: R26.2, U$9.21 (DIGIN2)
unnamed: R27.2, U$9.25 (CURRENT)
unnamed: R28.2, U$10.20 (DIGIN1)
unnamed: R29.2, U$10.21 (DIGIN2)
unnamed: R30.2, U$10.25 (CURRENT)
unnamed: R33.1, T3.3 (C), U$11.P$1 (G)
unnamed: SOLENOID2.P$2 (2), U$11.P$2 (C)
unnamed: BOOST_EN.1, U$15.3 (C)
unnamed: R36.1, U$15.1 (B)
SCK: COM1.SCK, COM2.SCK, COM3.SCK, ENC1.5 (SCK), ENC2.5 (SCK), ENC3.5 (SCK), ENC4.5 (SCK), MAPLE.X30 (30)
VBOOST: POWERCAP1.P$2 (2), POWERCAP2.P$2 (2), R34.2, SOLENOID1.P$1 (1), SOLENOID2.P$1 (1), U$5.OUT+
VCC: CA2.1, CA4.1, CA5.1, CA6.1, CA7.1, ENC1.14 (VDD), ENC2.14 (VDD), ENC3.14 (VDD), ENC4.14 (VDD), R17.1, R20.1, R23.1, R26.1, R29.1, REG5V.P$3 (OUT), U$4.+, U$6.11 (VCC), U$7.11 (VCC), U$8.11 (VCC), U$9.11 (VCC), U$10.11 (VCC), X1.5, X2.5, X3.5, X4.5, X5.5
VIN: R3.2, R5.1, R33.2, REG3.3V.P$1 (IN), REG5V.P$1 (IN), U$5.VIN (IN+), U$6.7 (VIN), U$6.8 (VIN), U$7.7 (VIN), U$7.8 (VIN), U$8.7 (VIN), U$8.8 (VIN), U$9.7 (VIN), U$9.8 (VIN), U$10.7 (VIN), U$10.8 (VIN), XT1.V+, XT60.V+

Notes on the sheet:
POWER
MCU
BUZZER
KICKER
INFRARED

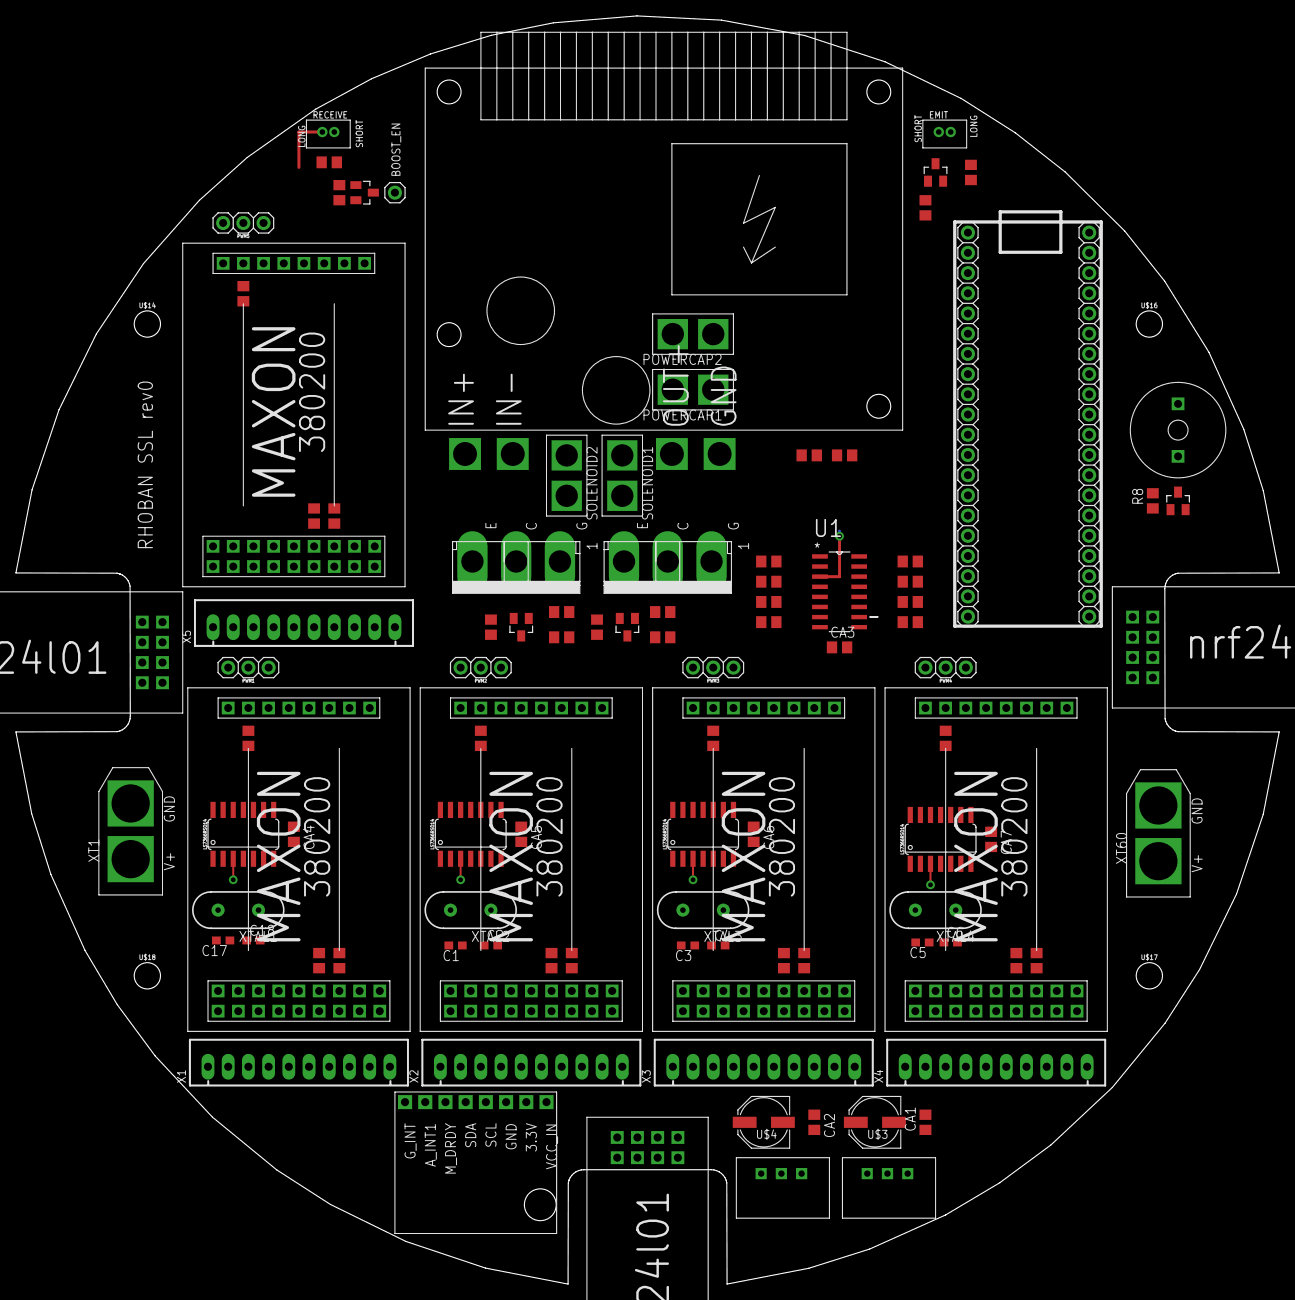
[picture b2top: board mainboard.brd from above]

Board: 2 copper layers, 158.8 x 159.4 mm, 106 parts (0 on the bottom side), 116 nets.

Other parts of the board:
U$14, U$16, U$17, U$18: STAND-OFF

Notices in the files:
parts and their libraries:
SparkFun-Capacitors: Licensing: Creative Commons ShareAlike 4.0 International - https://creativecommons.org/licenses/by-sa/4.0
SparkFun-Passives: Licensing: CC v3.0 Share-Alike You are welcome to use this library for commercial purposes.
